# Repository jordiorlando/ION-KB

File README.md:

# ION-KB
A 19/44/70-key mechanical keyboard with lots of goodies

[Google Doc](https://docs.google.com/document/d/1FTBsirHFBGyqN_NbH0D3qjMs6BySK3XLYaDQEiHJNy0/edit?usp=sharing)

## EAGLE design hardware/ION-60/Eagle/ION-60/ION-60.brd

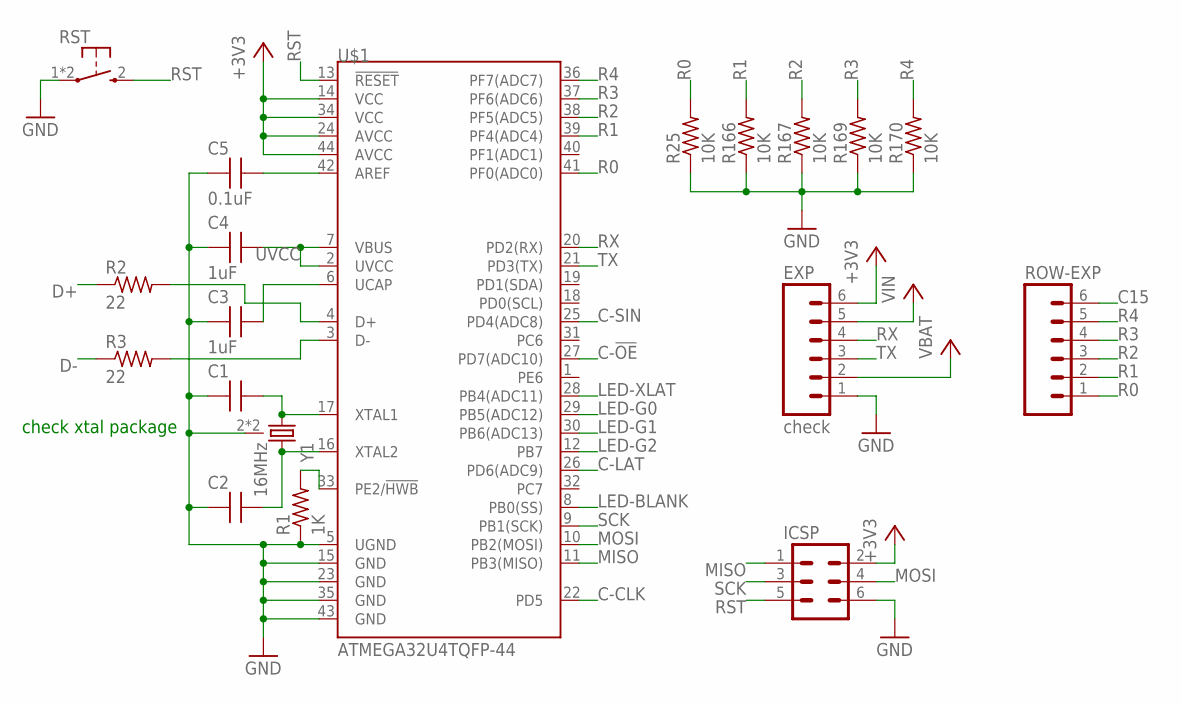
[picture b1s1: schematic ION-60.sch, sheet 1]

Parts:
C1, C2: CAPACITOR0603; C0603
C3, C4: 1uF; C0603
C5: 0.1uF; C0603
EXP: check; M-1X06-0.05-PTH
ICSP: 2X03M-0.1-PTH-SHROUDED; M-2X03-0.1-PTH-SHROUDED
R1: 1K; R0603
R2, R3: 22; R0603
R25, R166, R167, R169, R170: 10K; R0603
ROW-EXP: 1X06M-0.1-PTH; M-1X06-0.1-PTH
RST: SWITCH-TACTILESMD-RA; SWITCH-TACTILE-SMD-RA
U$1: ATMEGA32U4TQFP-44; TQFP44
Y1: 16MHz; CRYSTAL-SMD-3.2X2.5

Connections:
+3V3: EXP.6, ICSP.2, U$1.14 (VCC), U$1.24 (AVCC), U$1.34 (VCC), U$1.44 (AVCC); also elsewhere on the board
C15: ROW-EXP.6; also elsewhere on the board
C-!OE: U$1.27 (PD7(ADC10)); also elsewhere on the board
C-CLK: U$1.22 (PD5); also elsewhere on the board
C-LAT: U$1.26 (PD6(ADC9)); also elsewhere on the board
C-SIN: U$1.25 (PD4(ADC8)); also elsewhere on the board
D+: R2.1; also elsewhere on the board
D-: R3.1; also elsewhere on the board
GND: C1.1, C2.1, C3.1, C4.1, C5.1, EXP.1, ICSP.6, R1.1, R25.1, R166.1, R167.1, R169.1, R170.1, RST.1, RST.3 (1), U$1.5 (UGND), U$1.15 (GND), U$1.23 (GND), U$1.35 (GND), U$1.43 (GND), Y1.2 (GND), Y1.4 (GND); also elsewhere on the board
LED-BLANK: U$1.8 (PB0(SS)); also elsewhere on the board
LED-G0: U$1.29 (PB5(ADC12)); also elsewhere on the board
LED-G1: U$1.30 (PB6(ADC13)); also elsewhere on the board
LED-G2: U$1.12 (PB7); also elsewhere on the board
LED-XLAT: U$1.28 (PB4(ADC11)); also elsewhere on the board
MISO: ICSP.1, U$1.11 (PB3(MISO))
MOSI: ICSP.4, U$1.10 (PB2(MOSI)); also elsewhere on the board
unnamed: C1.2, U$1.17 (XTAL1), Y1.1
unnamed: C2.2, U$1.16 (XTAL2), Y1.3 (2)
unnamed: R1.2, U$1.33 (PE2/!HWB)
unnamed: C3.2, U$1.6 (UCAP)
unnamed: C5.2, U$1.42 (AREF)
unnamed: R2.2, U$1.4 (D+)
unnamed: R3.2, U$1.3 (D-)
R0: R25.2, ROW-EXP.1, U$1.41 (PF0(ADC0)); also elsewhere on the board
R1: R166.2, ROW-EXP.2, U$1.39 (PF4(ADC4)); also elsewhere on the board
R2: R167.2, ROW-EXP.3, U$1.38 (PF5(ADC5)); also elsewhere on the board
R3: R169.2, ROW-EXP.4, U$1.37 (PF6(ADC6)); also elsewhere on the board
R4: R170.2, ROW-EXP.5, U$1.36 (PF7(ADC7)); also elsewhere on the board
RST: ICSP.5, RST.2 (3), U$1.13 (!RESET)
RX: EXP.4, U$1.20 (PD2(RX))
SCK: ICSP.3, U$1.9 (PB1(SCK)); also elsewhere on the board
TX: EXP.3, U$1.21 (PD3(TX))
UVCC: C4.2, U$1.2 (UVCC), U$1.7 (VBUS)
VBAT: EXP.2; also elsewhere on the board
VIN: EXP.5; also elsewhere on the board

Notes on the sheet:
check xtal package

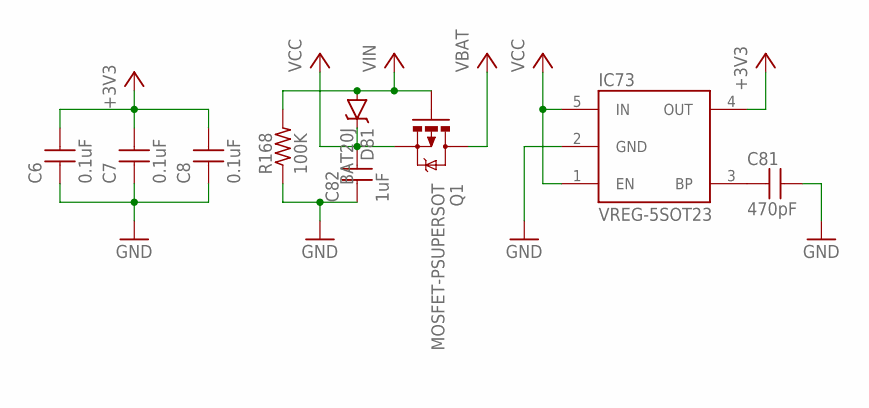
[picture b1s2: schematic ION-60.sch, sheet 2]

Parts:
C6, C7, C8: 0.1uF; C0603
C81: 470pF; C0603
C82: 1uF; C0603
D81: BAT20J; SOD-323
IC73: VREG-5SOT23; SOT23-5
Q1: MOSFET-PSUPERSOT; SUPERSOT-3
R168: 100K; R0603

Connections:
+3V3: C6.2, C7.2, C8.2, IC73.4 (OUT); also elsewhere on the board
GND: C6.1, C7.1, C8.1, C81.2, C82.1, IC73.2 (GND), R168.1; also elsewhere on the board
unnamed: C81.1, IC73.3 (BP)
VBAT: Q1.3 (D); also elsewhere on the board
VCC: C82.2, D81.C, IC73.1 (EN), IC73.5 (IN), Q1.2 (S)
VIN: D81.A, Q1.1 (G), R168.2; also elsewhere on the board

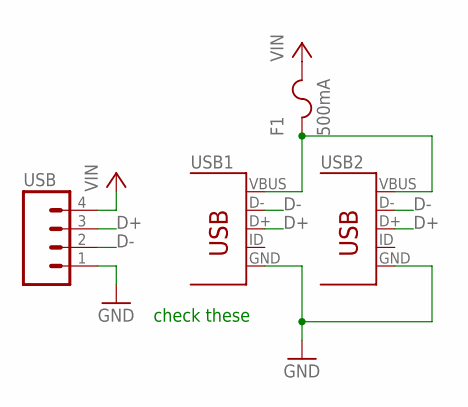
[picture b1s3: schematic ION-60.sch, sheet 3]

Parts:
F1: 500mA; FUSE-1812
USB: 1X04M-0.1-PTH; M-1X04-0.1-PTH
USB1, USB2: USB-MICROBSMD; USB-MICRO-B-SMD

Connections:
D+: USB.3, USB1.D+, USB2.D+; also elsewhere on the board
D-: USB.2, USB1.D-, USB2.D-; also elsewhere on the board
GND: USB.1, USB1.GND, USB2.GND; also elsewhere on the board
unnamed: F1.1, USB1.VBUS, USB2.VBUS
VIN: F1.2, USB.4; also elsewhere on the board

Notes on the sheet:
check these

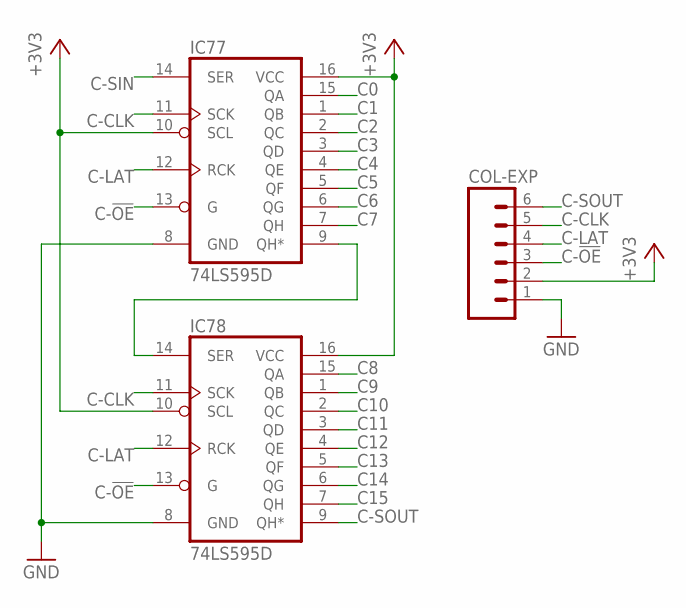
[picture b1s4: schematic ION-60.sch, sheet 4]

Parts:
COL-EXP: 1X06M-0.05-PTH; M-1X06-0.05-PTH
IC77, IC78: 74LS595D; SO16

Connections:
+3V3: COL-EXP.2, IC77.10 (SCL), IC77.16 (VCC), IC78.10 (SCL), IC78.16 (VCC); also elsewhere on the board
C0: IC77.15 (QA); also elsewhere on the board
C1: IC77.1 (QB); also elsewhere on the board
C2: IC77.2 (QC); also elsewhere on the board
C3: IC77.3 (QD); also elsewhere on the board
C4: IC77.4 (QE); also elsewhere on the board
C5: IC77.5 (QF); also elsewhere on the board
C6: IC77.6 (QG); also elsewhere on the board
C7: IC77.7 (QH); also elsewhere on the board
C8: IC78.15 (QA); also elsewhere on the board
C9: IC78.1 (QB); also elsewhere on the board
C10: IC78.2 (QC); also elsewhere on the board
C11: IC78.3 (QD); also elsewhere on the board
C12: IC78.4 (QE); also elsewhere on the board
C13: IC78.5 (QF); also elsewhere on the board
C14: IC78.6 (QG); also elsewhere on the board
C15: IC78.7 (QH); also elsewhere on the board
C-!OE: COL-EXP.3, IC77.13 (G), IC78.13 (G); also elsewhere on the board
C-CLK: COL-EXP.5, IC77.11 (SCK), IC78.11 (SCK); also elsewhere on the board
C-LAT: COL-EXP.4, IC77.12 (RCK), IC78.12 (RCK); also elsewhere on the board
C-SIN: IC77.14 (SER); also elsewhere on the board
C-SOUT: COL-EXP.6, IC78.9 (QH*)
GND: COL-EXP.1, IC77.8 (GND), IC78.8 (GND); also elsewhere on the board
unnamed: IC77.9 (QH*), IC78.14 (SER)

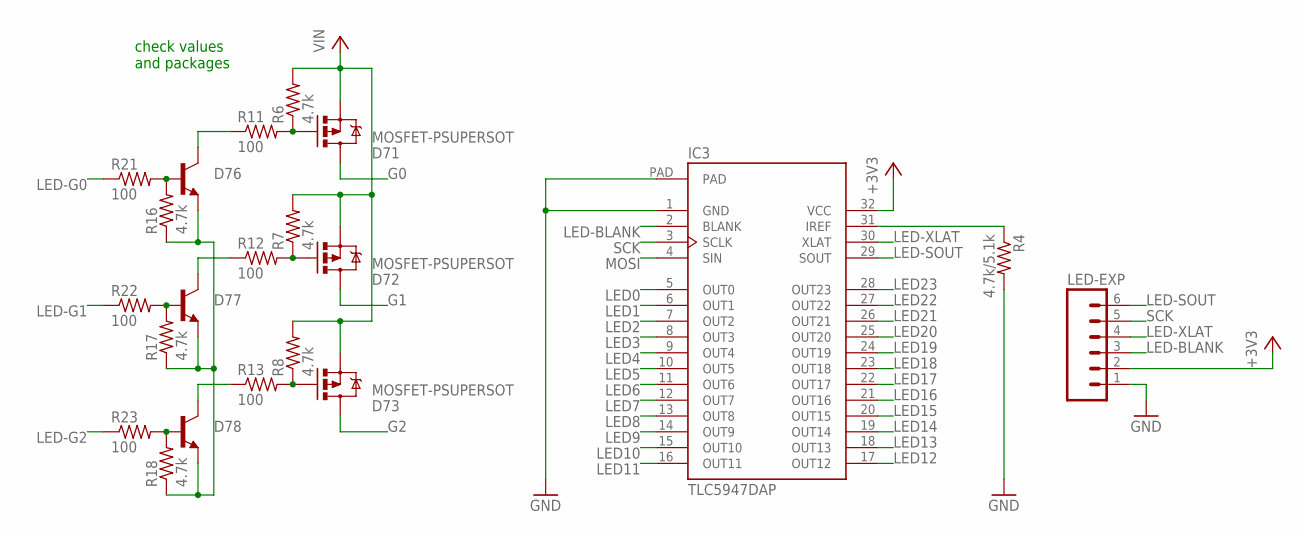
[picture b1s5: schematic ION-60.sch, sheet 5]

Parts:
D71, D72, D73: MOSFET-PSUPERSOT; SUPERSOT-3
D76, D77, D78: BSS138SOT23; SOT23
IC3: TLC5947DAP; HTSSOP-32
LED-EXP: 1X06M-0.05-PTH; M-1X06-0.05-PTH
R4: 4.7k/5.1k; R0603
R6, R7, R8, R16, R17, R18: 4.7k; R0603
R11, R12, R13, R21, R22, R23: 100; R0603

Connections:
+3V3: IC3.32 (VCC), LED-EXP.2; also elsewhere on the board
G0: D71.3 (D); also elsewhere on the board
G1: D72.3 (D); also elsewhere on the board
G2: D73.3 (D); also elsewhere on the board
GND: IC3.1 (GND), IC3.PAD, LED-EXP.1, R4.2; also elsewhere on the board
LED0: IC3.5 (OUT0); also elsewhere on the board
LED1: IC3.6 (OUT1); also elsewhere on the board
LED2: IC3.7 (OUT2); also elsewhere on the board
LED3: IC3.8 (OUT3); also elsewhere on the board
LED4: IC3.9 (OUT4); also elsewhere on the board
LED5: IC3.10 (OUT5); also elsewhere on the board
LED6: IC3.11 (OUT6); also elsewhere on the board
LED7: IC3.12 (OUT7); also elsewhere on the board
LED8: IC3.13 (OUT8); also elsewhere on the board
LED9: IC3.14 (OUT9); also elsewhere on the board
LED10: IC3.15 (OUT10); also elsewhere on the board
LED11: IC3.16 (OUT11); also elsewhere on the board
LED12: IC3.17 (OUT12); also elsewhere on the board
LED13: IC3.18 (OUT13); also elsewhere on the board
LED14: IC3.19 (OUT14); also elsewhere on the board
LED15: IC3.20 (OUT15); also elsewhere on the board
LED16: IC3.21 (OUT16); also elsewhere on the board
LED17: IC3.22 (OUT17); also elsewhere on the board
LED18: IC3.23 (OUT18); also elsewhere on the board
LED19: IC3.24 (OUT19); also elsewhere on the board
LED20: IC3.25 (OUT20); also elsewhere on the board
LED21: IC3.26 (OUT21); also elsewhere on the board
LED22: IC3.27 (OUT22); also elsewhere on the board
LED23: IC3.28 (OUT23); also elsewhere on the board
LED-BLANK: IC3.2 (BLANK), LED-EXP.3; also elsewhere on the board
LED-G0: R21.1; also elsewhere on the board
LED-G1: R22.1; also elsewhere on the board
LED-G2: R23.1; also elsewhere on the board
LED-SOUT: IC3.29 (SOUT), LED-EXP.6
LED-XLAT: IC3.30 (XLAT), LED-EXP.4; also elsewhere on the board
MOSI: IC3.4 (SIN); also elsewhere on the board
unnamed: D76.3 (E), D77.3 (E), D78.3 (E), R16.1, R17.1, R18.1
unnamed: IC3.31 (IREF), R4.1
unnamed: D71.1 (G), R6.1, R11.2
unnamed: D73.1 (G), R8.1, R13.2
unnamed: D72.1 (G), R7.1, R12.2
unnamed: D76.2 (C), R11.1
unnamed: D77.1 (B), R17.2, R22.2
unnamed: D78.2 (C), R13.1
unnamed: D77.2 (C), R12.1
unnamed: D76.1 (B), R16.2, R21.2
unnamed: D78.1 (B), R18.2, R23.2
SCK: IC3.3 (SCLK), LED-EXP.5; also elsewhere on the board
VIN: D71.2 (S), D72.2 (S), D73.2 (S), R6.2, R7.2, R8.2; also elsewhere on the board

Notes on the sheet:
check values and packages

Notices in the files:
parts and their libraries:
SparkFun-DigitalIC: Licensing: Creative Commons ShareAlike 4.0 International - https://creativecommons.org/licenses/by-sa/4.0
